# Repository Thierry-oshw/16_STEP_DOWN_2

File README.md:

# 16_STEP_DOWN_2
 DCDC step down with MP2359Dj-LF-Z

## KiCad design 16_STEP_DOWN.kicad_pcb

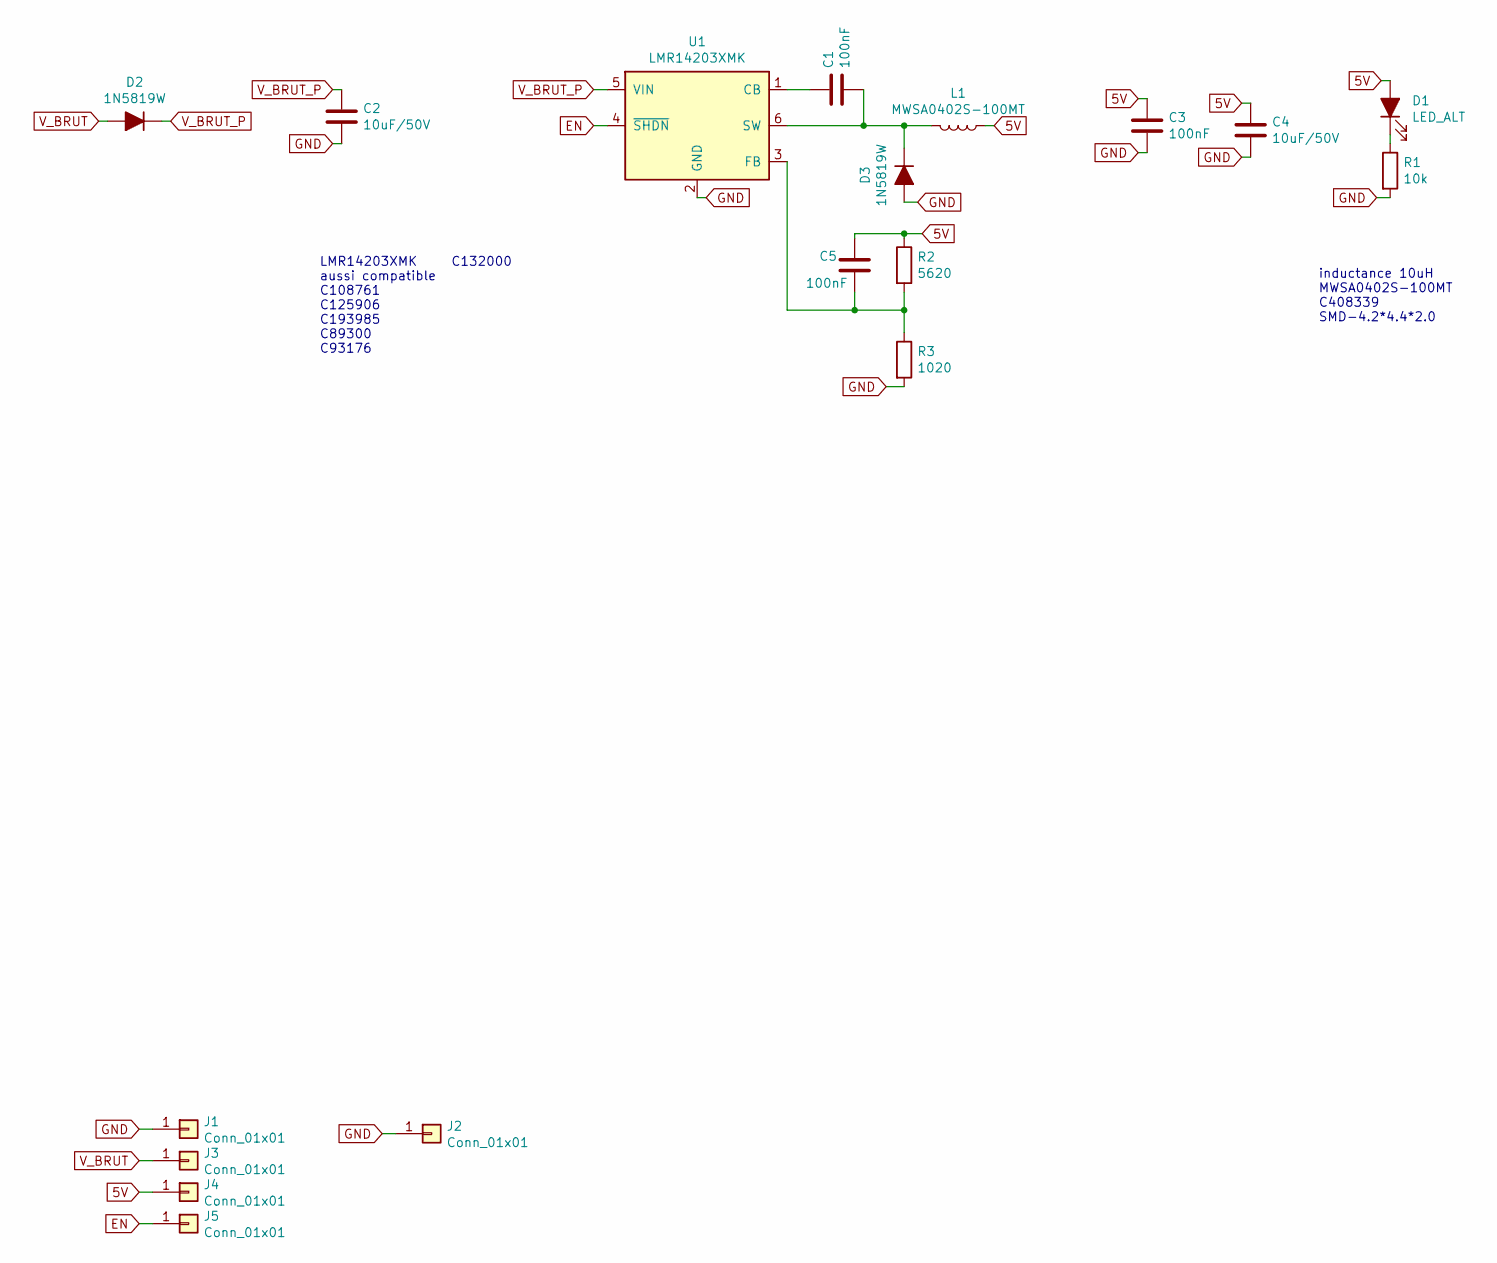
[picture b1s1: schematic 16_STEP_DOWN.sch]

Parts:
C1, C3, C5: 100nF; C_0603_1608Metric
C2, C4: 10uF/50V; C_1210_3225Metric
D1: LED_ALT; D_0603_1608Metric
D2, D3: 1N5819W; D_SOD-123F
J1, J2, J3, J4, J5: Conn_01x01; Castellated_conn
L1: MWSA0402S-100MT; L_Sunlord_MWSA0402S_4.2x4.4x2.0mm
R1: 10k; R_0603_1608Metric
R2: 5620; R_0603_1608Metric
R3: 1020; R_0603_1608Metric
U1: LMR14203XMK; SOT-23-6

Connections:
5V: C3.1, C4.1, C5.1, D1.2 (A), J4.1, L1.1, R2.1
EN: J5.1, U1.4 (~SHDN)
GND: C2.2, C3.2, C4.2, D3.2 (A), J1.1, J2.1, R1.2, R3.2, U1.2 (GND)
unnamed: C1.1, U1.1 (CB)
unnamed: C1.2, D3.1 (K), L1.2, U1.6 (SW)
unnamed: C5.2, R2.2, R3.1, U1.3 (FB)
unnamed: D1.1 (K), R1.1
V_BRUT: D2.2 (A), J3.1
V_BRUT_P: C2.1, D2.1 (K), U1.5 (VIN)

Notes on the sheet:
inductance 10uH MWSA0402S-100MT C408339 SMD-4.2*4.4*2.0
LMR14203XMK C132000 aussi compatible C108761 C125906 C193985 C89300 C93176

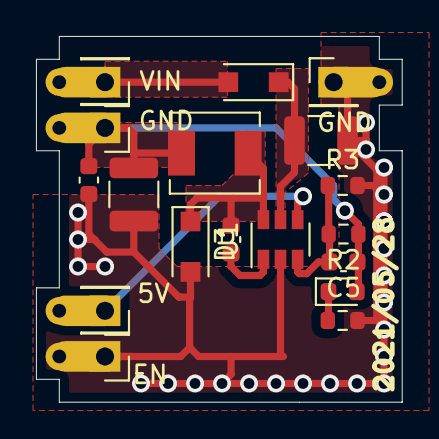
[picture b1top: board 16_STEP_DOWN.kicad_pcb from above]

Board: 2 copper layers, 20.3 x 20.3 mm, 18 parts (0 on the bottom side), 9 nets.

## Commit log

2021-06-07 schéma + routage
2021-06-07 ajout liste compatible
2021-07-26 maj split librairies
2023-05-02 chgt nom fichier licence
